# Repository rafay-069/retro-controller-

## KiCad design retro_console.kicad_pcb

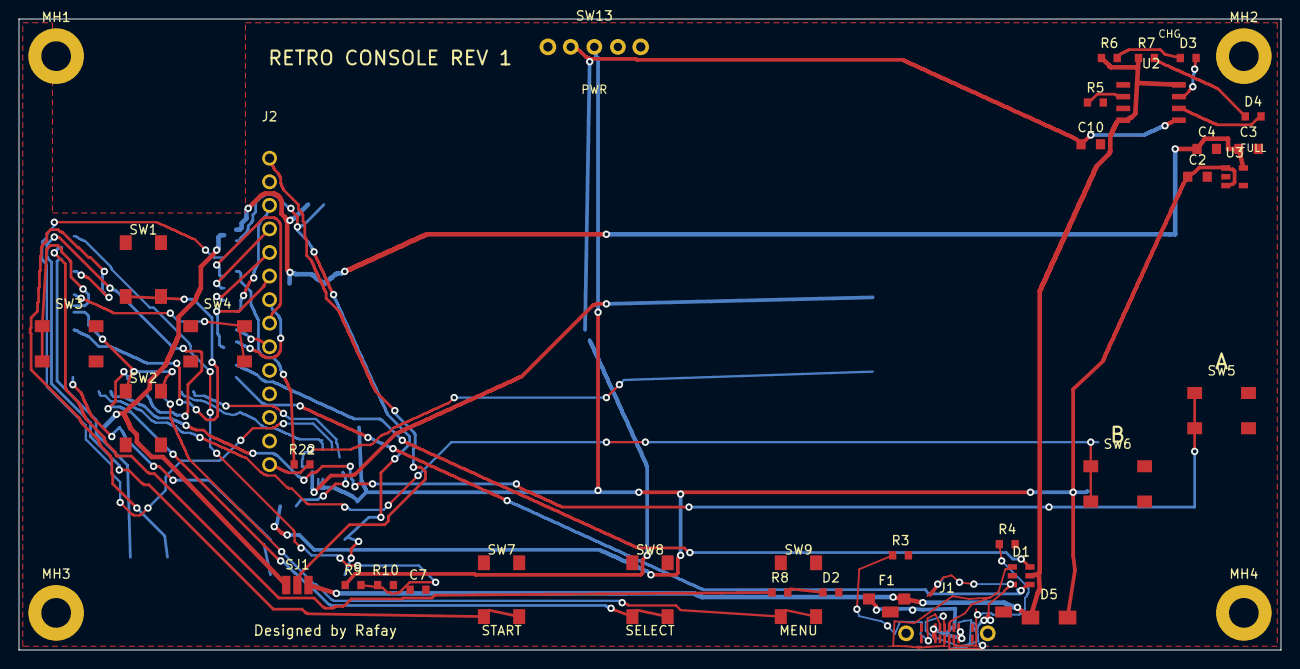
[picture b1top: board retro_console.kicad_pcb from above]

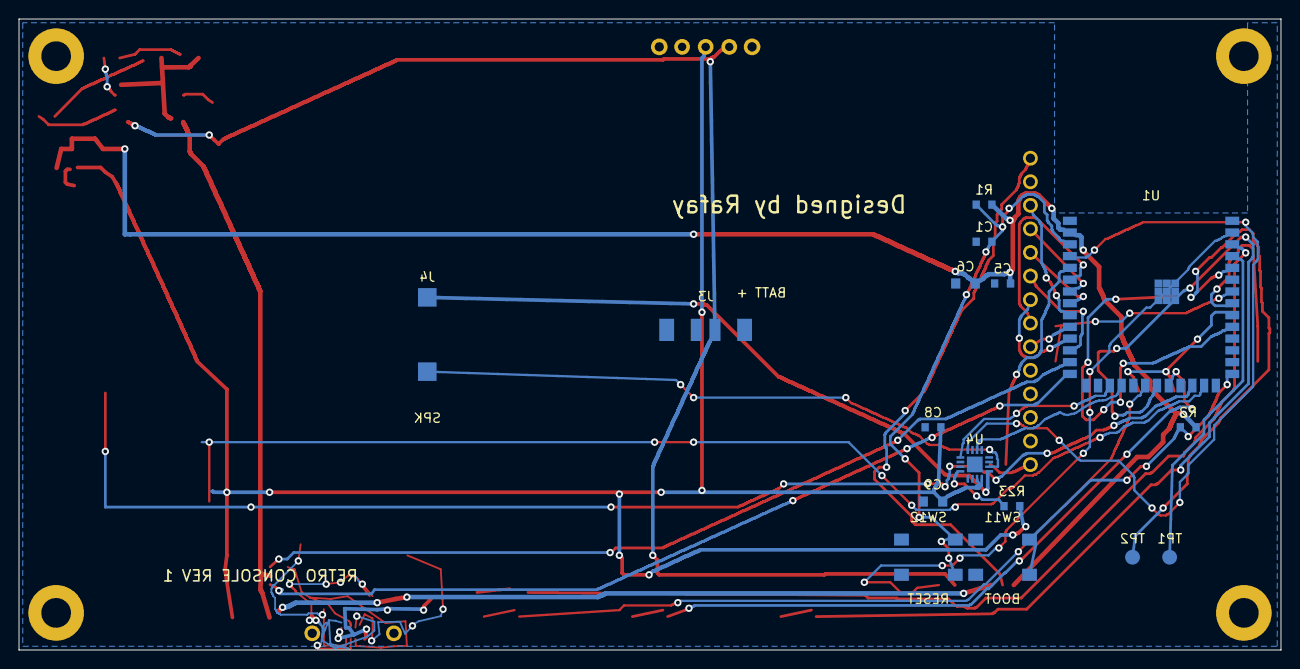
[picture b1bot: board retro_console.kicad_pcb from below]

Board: 3 copper layers, 136.0 x 68.0 mm, 55 parts (16 on the bottom side), 51 nets.

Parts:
C1: C1U; C1
C2: C10U; C2
C3: C10U; C3
C4: C22U; C4
C5: C100N; C5
C6: C10U; C6
C7: C100N; C7
C8: C100N; C8
C9: C10U; C9
C10: C10U; C10
D1: USBLC6-2SC6; D1
D2: LED_RED; D2
D3: LED_RED; D3
D4: LED_GRN; D4
D5: SS14; D5
F1: PTC1A1; F1
J1: USB_C_16P; J1
J2: SCR_1x14; J2
J3: B2B-PH-SM4-TB; J3
J4: SPK_PADS; J4
MH1: M3; MH1
MH2: M3; MH2
MH3: M3; MH3
MH4: M3; MH4
R1: R10K; R1
R2: R10K; R2
R3: R5K1; R3
R4: R5K1; R4
R5: R2K; R5
R6: R1K; R6
R7: R1K; R7
R8: R1K; R8
R9: R100K; R9
R10: R100K; R10
R22: R1K; R22
R23: R1M; R23
SJ1: JUMPER3; SJ1
SW1: TACT6x6; SW1
SW2: TACT6x6; SW2
SW3: TACT6x6; SW3
SW4: TACT6x6; SW4
SW5: TACT6x6; SW5
SW6: TACT6x6; SW6
SW7: TACT6x6; SW7
SW8: TACT6x6; SW8
SW9: TACT6x6; SW9
SW11: TACT6x6; SW11
SW12: TACT6x6; SW12
SW13: SS-12D10; SW13
TP1: TP; TP1
TP2: TP; TP2
U1: ESP32-S3-WROOM-1-N16R8; U1
U2: TP4056; U2
U3: ME6211C33; U3
U4: MAX98357A; U4

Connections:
+3V3: C3.1, C4.1, C5.1, C6.1, R1.1, R2.1, SJ1.1, U1.2, U3.5
+BATT: C10.1, J3.1, R9.1, SW13.1, U2.5
AMP_SD: R23.2, U4.4
BATT_ADC: C7.1, R9.2, R10.1, U1.39
BOOT: R2.2, SW11.1, SW11.2, U1.27
BTN_A: SW5.1, SW5.2, U1.24
BTN_B: SW6.1, SW6.2, U1.25
BTN_DOWN: SW2.1, SW2.2, U1.32
BTN_LEFT: SW3.1, SW3.2, U1.33
BTN_MENU: SW9.1, SW9.2, U1.20
BTN_RIGHT: SW4.1, SW4.2, U1.34
BTN_SELECT: SW8.1, SW8.2, U1.22
BTN_START: SW7.1, SW7.2, U1.21
BTN_UP: SW1.1, SW1.2, U1.31
CC1: J1.A5, R3.1
CC2: J1.B5, R4.1
CHRG: D3.2, U2.7
EN: C1.1, R1.2, SW12.1, SW12.2, U1.3
GND: C1.2, C2.2, C3.2, C4.2, C5.2, C6.2, C7.2, C8.2, C9.2, C10.2, D1.2, D2.2, J1.A1, J1.A12, J1.B1, J1.B12, J1.S1, J1.S2, J1.S3, J1.S4, J2.2, J3.2, R3.2, R4.2, R5.2, R10.2, SW1.3, SW1.4, SW2.3, SW2.4, SW3.3, SW3.4, SW4.3, SW4.4, SW5.3, SW5.4, SW6.3, SW6.4, SW7.3, SW7.4, SW8.3, SW8.4, SW9.3, SW9.4, SW11.3, SW11.4, SW12.3, SW12.4, U1.1, U1.40, U1.41, U2.1, U2.3, U3.2, U4.2, U4.3, U4.11, U4.15, U4.17
I2S_BCK: U1.4, U4.16
I2S_DOUT: U1.17, U4.1
I2S_WS: U1.18, U4.14
LCD_BL: J2.8, U1.6
LCD_CS: J2.3, U1.9
LCD_DC: J2.5, U1.8
LCD_RST: J2.4, U1.7
LCD_VCC: J2.1, SJ1.2
LED2_A: D3.1, R6.2
LED3_A: D4.1, R7.2
LED_A: D2.1, R8.2
LED_STAT: R8.1, U1.38
MECH: J3.3, J3.4, MH1.1, MH2.1, MH3.1, MH4.1, SW13.4, SW13.5
NC_MAX: U4.5, U4.6, U4.12, U4.13
PROG: R5.1, U2.2
RXD0: TP2.1, U1.36
SD_CS: R22.1, U1.5
SD_CS_M: J2.14, R22.2
SPI_MISO: J2.9, U1.10
SPI_MOSI: J2.6, U1.12
SPI_SCK: J2.7, U1.11
SPK_N: J4.2, U4.10
SPK_P: J4.1, U4.9
STDBY: D4.2, U2.6
TXD0: TP1.1, U1.37
USB_DM: D1.6, U1.13
USB_DM_C: D1.1, J1.A7, J1.B7
USB_DP: D1.4, U1.14
USB_DP_C: D1.3, J1.A6, J1.B6
VBUS: D1.5, D5.1, F1.2, R6.1, R7.1, SJ1.3, U2.4, U2.8
VBUS_IN: F1.1, J1.A4, J1.A9, J1.B4, J1.B9
VSYS: C2.1, C8.1, C9.1, D5.2, R23.1, SW13.2, U3.1, U3.3, U4.7, U4.8
